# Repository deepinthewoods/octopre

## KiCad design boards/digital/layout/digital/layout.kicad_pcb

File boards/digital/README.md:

# digital

## Description

<!-- Brief description of this board -->

## Features

-

## Build Instructions

```bash
pcb build boards/digital
pcb layout boards/digital
```

## License

<!-- Add license information -->

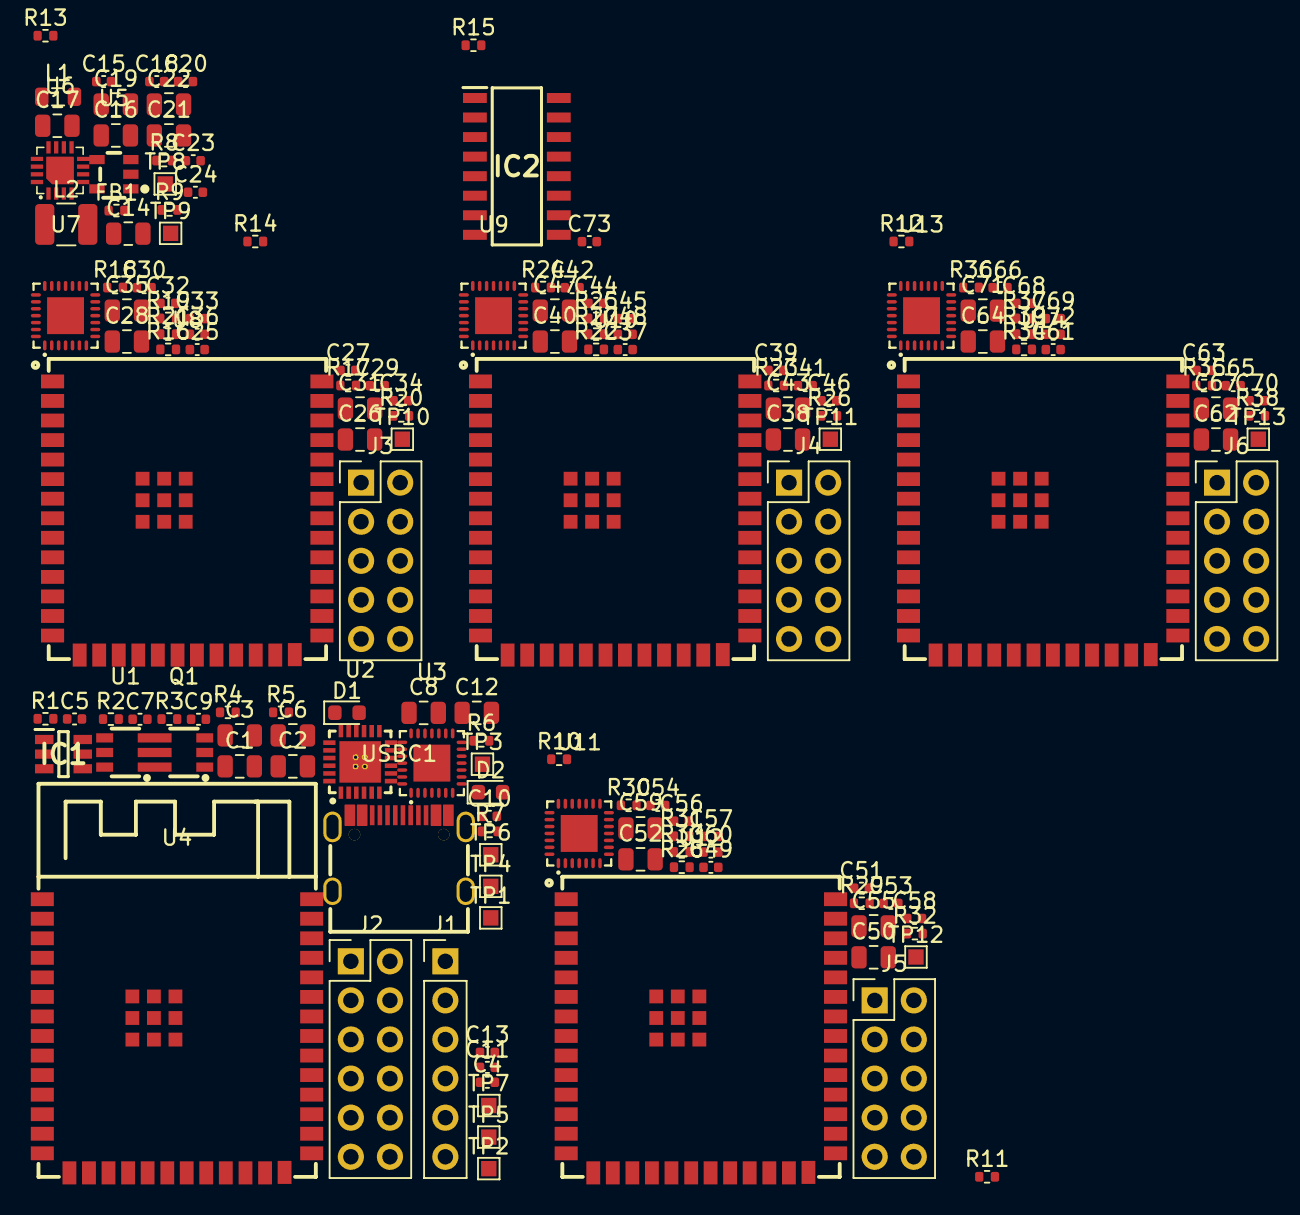
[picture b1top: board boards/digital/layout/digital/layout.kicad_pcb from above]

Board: 6 copper layers, 154 parts (0 on the bottom side), 144 nets, no tracks yet.

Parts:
C1, C2, C3, C6, C8, C12, C14, C16, C17, C19, C26, C28, C31, C35, C38, C40, C43, C47, C50, C52, C55, C59, C62, C64, C67, C71: GRM21BZ71E106KE15K; C_0805_2012Metric
C4, C5, C7, C9, C10, C11, C13, C15, C18, C20, C23, C25, C27, C29, C30, C32, C33, C34, C36, C37, C39, C41, C42, C44, C45, C46, C48, C49, C51, C53, C54, C56, C57, C58, C60, C61, C63, C65, C66, C68, C69, C70, C72, C73: GCM155R71H104KE02D; C_0402_1005Metric
C21, C22: GRM21BZ71A226ME15K; C_0805_2012Metric
C24: GRM1555CYA103GE01D; C_0402_1005Metric
D1, D2: LED GREEN; LED_0603_1608Metric
FB1: 600 100MHz; R_0402_1005Metric
IC1: USBLC6-2SC6
IC2: 74HC4052D
J1: 61300611121; PinHeader_1x06_P2.54mm_Vertical
J2: 2.54mm 6 x 2 THT Vertical Male; PinHeader_2x06_P2.54mm_Vertical
J3, J4, J5, J6: 61301021121; PinHeader_2x05_P2.54mm_Vertical
L1: 10uH; L_0805_2012Metric
L2: 2.2uH; L_1210_3225Metric
Q1: FS8205A
R1, R2: ERJ-2RKF5101X; R_0402_1005Metric
R3: ERJ-2RKF1202X; R_0402_1005Metric
R4: ERJ-2RKF1001X; R_0402_1005Metric
R5, R6, R16, R17, R22, R23, R28, R29, R34, R35: ERJ-2GE0R00X; R_0402_1005Metric
R7, R18, R19, R24, R25, R30, R31, R36, R37: ERJ-2RKF1002X; R_0402_1005Metric
R8: 64k; R_0402_1005Metric
R9: ERJ-2RKF2003X; R_0402_1005Metric
R10, R11, R12, R13, R14, R15, R20, R21, R26, R27, R32, R33, R38, R39: ERJ-2RKF33R0X; R_0402_1005Metric
TP1, TP2, TP3, TP4, TP5, TP6, TP7, TP8, TP9, TP10, TP11, TP12, TP13: ?; TestPoint_Pad_1.0x1.0mm
U1: HY2120-CB
U2: ?; SC8922QDLR
U3, U7, U9, U11, U13: ES8388
U4: ESP32-S3-WROOM-1-N16R8
U5: TPS7A2033PDBVR
U6: TPS62140RGTR
U8, U10, U12, U14: ESP32-S3-WROOM-1U-N16R8
USBC1: TYPE-C-31-M-12

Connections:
3V3_ANA: C16.1, FB1.1, L1.2, R5.1, R16.1, R22.1, R28.1, R34.1, TP8.1
3V3_DIG: C3.1, C4.1, C21.1, C22.1, C23.1, C31.1, C32.1, C43.1, C44.1, C55.1, C56.1, C67.1, C68.1, C73.1, D2.2, FB1.2, IC2.16, J1.6, L2.2, R4.1, R6.1, R7.1, R7.2, R9.1, R17.1, R18.1, R19.1, R23.1, R24.1, R25.1, R29.1, R30.1, R31.1, R35.1, R36.1, R37.1, TP9.1, U3.26, U4.2, U4.3, U4.27, U6.14, U7.26, U8.2, U9.26, U10.2, U11.26, U12.2, U13.26, U14.2
GND: C1.2, C2.2, C3.2, C4.2, C5.2, C6.2, C7.2, C8.2, C9.2, C10.2, C11.2, C12.2, C13.2, C14.2, C15.2, C16.2, C17.2, C18.2, C19.2, C20.2, C21.2, C22.2, C23.2, C24.2, C25.2, C26.2, C27.2, C28.2, C29.2, C30.2, C31.2, C32.2, C33.2, C34.2, C35.2, C36.2, C37.2, C38.2, C39.2, C40.2, C41.2, C42.2, C43.2, C44.2, C45.2, C46.2, C47.2, C48.2, C49.2, C50.2, C51.2, C52.2, C53.2, C54.2, C55.2, C56.2, C57.2, C58.2, C59.2, C60.2, C61.2, C62.2, C63.2, C64.2, C65.2, C66.2, C67.2, C68.2, C69.2, C70.2, C71.2, C72.2, C73.2, D1.1, D2.1, IC1.2, IC2.6, IC2.7, IC2.8, J1.5, J2.1, J2.2, J2.9, J2.10, J3.1, J3.2, J3.7, J3.8, J4.1, J4.2, J4.7, J4.8, J5.1, J5.2, J5.7, J5.8, J6.1, J6.2, J6.7, J6.8, Q1.1, R1.2, R2.2, R3.2, R8.2, U1.3, U1.6, U2.7, U2.10, U2.25, U3.4, U3.13, U3.18, U3.29, U4.1, U4.40, U4.41, U5.2, U6.6, U6.7, U6.8, U6.15, U6.16, U6.17, U7.4, U7.13, U7.18, U7.29, U8.1, U8.40, U8.41, U9.4, U9.13, U9.18, U9.29, U10.1, U10.40, U10.41, U11.4, U11.13, U11.18, U11.29, U12.1, U12.40, U12.41, U13.4, U13.13, U13.18, U13.29, U14.1, U14.40, U14.41, USBC1.1, USBC1.2, USBC1.3, USBC1.4, USBC1.A1B12, USBC1.B1A12
MASTER.BAT_PROT_POS: Q1.4, Q1.6, U1.1, U1.2
MASTER.BAT_RAW_POS: Q1.2, Q1.5, U1.4, U1.5
MASTER.CHG_SW: U2.1, U2.2, U2.23, U2.24
MASTER.JTAG_TCK: J1.3, U4.24
MASTER.JTAG_TDI: J1.1, U4.26
MASTER.JTAG_TDO: J1.2, U4.16
MASTER.JTAG_TMS: J1.4, U4.25
MASTER.M_ES_ADCVREF: C5.1, U3.19
MASTER.M_ES_AVDD: C6.1, C7.1, C10.1, C11.1, R5.2, U3.3, U3.16, U3.17
MASTER.M_ES_DVDD: C8.1, C9.1, R6.2, U3.2
MASTER.M_ES_VMID: C12.1, U3.20
MASTER.M_ES_VREF: C13.1, U3.10
MASTER.M_I2S_BCLK: U3.5, U4.5
MASTER.M_I2S_LRCLK: U3.7, U4.6
MASTER.M_I2S_MCLK: U3.1, U4.4
MASTER.M_I2S_SDIN: U3.6, U4.7
MASTER.M_I2S_SDOUT: U3.8, U4.12
MASTER.PG_CHG: D1.2, R4.2, U2.8
MASTER.USB_CC1: R1.1, USBC1.A5
MASTER.USB_CC2: R2.1, USBC1.B5
MASTER.USB_DN: IC1.3, IC1.4, TP4.1, U4.35, USBC1.A7, USBC1.B7
MASTER.USB_DP: IC1.1, IC1.6, TP5.1, U4.34, USBC1.A6, USBC1.B6
MASTER.USB_VBUS: C1.1, IC1.5, U2.4, USBC1.A4B9, USBC1.B4A9
MASTER.VSYS: TP7.1, U2.20, U2.21, U2.22
MCLK_S1: R10.2, U8.7
MCLK_S2: R11.2, U10.7
MCLK_S3: R12.2, U12.7
MCLK_S4: R13.2, U14.7
MCLK_SRC: R10.1, R11.1, R12.1, R13.1, TP3.1, U4.8
MUX_A: IC2.10, U4.11
MUX_B: IC2.9, U4.13
MUX_RX: IC2.3, U4.10
MUX_TX: IC2.13, U4.9
M_5V_ANA: C14.1, C15.1, J2.12, U5.1, U5.3
M_AIN_L: J2.3, U3.24
M_AIN_R: J2.4, U3.23
M_DAC_L: J2.5, U3.12
M_DAC_R: J2.6, U3.11
M_HP_L: J2.7, U3.15
M_HP_R: J2.8, U3.14
PWR.3V3_ANA_FILT: C17.1, C18.1, L1.1, U5.5
PWR.DIG_BUCK_FB: R8.1, R9.2, U6.5
PWR.DIG_BUCK_SS: C24.1, U6.9
PWR.DIG_BUCK_SW: L2.1, U6.1, U6.2, U6.3
S1_AIN_L: J3.3, U7.24
S1_AIN_R: J3.4, U7.23
S1_DAC_L: J3.5, U7.12
S1_DAC_R: J3.6, U7.11
S1_PWM_L: J3.9, R20.2
S1_PWM_R: J3.10, R21.2
S2_AIN_L: J4.3, U9.24
S2_AIN_R: J4.4, U9.23
S2_DAC_L: J4.5, U9.12
S2_DAC_R: J4.6, U9.11
S2_PWM_L: J4.9, R26.2
S2_PWM_R: J4.10, R27.2
S3_AIN_L: J5.3, U11.24
S3_AIN_R: J5.4, U11.23
S3_DAC_L: J5.5, U11.12
S3_DAC_R: J5.6, U11.11
S3_PWM_L: J5.9, R32.2
S3_PWM_R: J5.10, R33.2
S4_AIN_L: J6.3, U13.24
S4_AIN_R: J6.4, U13.23
S4_DAC_L: J6.5, U13.12
S4_DAC_R: J6.6, U13.11
S4_PWM_L: J6.9, R38.2
S4_PWM_R: J6.10, R39.2
SLAVE1.ES_ADCVREF: C25.1, U7.19
SLAVE1.ES_AVDD: C26.1, C27.1, C33.1, C34.1, R16.2, U7.3, U7.16, U7.17
SLAVE1.ES_DVDD: C28.1, C29.1, R17.2, U7.2
SLAVE1.ES_VMID: C35.1, U7.20
SLAVE1.ES_VREF: C36.1, U7.10
SLAVE1.I2S_BCLK: U7.5, U8.38
SLAVE1.I2S_LRCLK: U7.7, U8.34
SLAVE1.I2S_MCLK: TP10.1, U7.1, U8.39
SLAVE1.I2S_SDIN: U7.6, U8.35
SLAVE1.I2S_SDOUT: U7.8, U8.33
SLAVE1.PWM_L_INT: R20.1, U8.21
SLAVE1.PWM_R_INT: R21.1, U8.22
SLAVE1_EN: C30.1, R18.2, U4.30, U8.3
SLAVE1_GPIO0: R19.2, U4.14, U8.27
SLAVE1_RX: IC2.1, U8.37
SLAVE1_TX: IC2.12, U8.36
SLAVE2.ES_ADCVREF: C37.1, U9.19
SLAVE2.ES_AVDD: C38.1, C39.1, C45.1, C46.1, R22.2, U9.3, U9.16, U9.17
SLAVE2.ES_DVDD: C40.1, C41.1, R23.2, U9.2
SLAVE2.ES_VMID: C47.1, U9.20
SLAVE2.ES_VREF: C48.1, U9.10
SLAVE2.I2S_BCLK: U9.5, U10.38
SLAVE2.I2S_LRCLK: U9.7, U10.34
SLAVE2.I2S_MCLK: TP11.1, U9.1, U10.39
SLAVE2.I2S_SDIN: U9.6, U10.35
SLAVE2.I2S_SDOUT: U9.8, U10.33
SLAVE2.PWM_L_INT: R26.1, U10.21
SLAVE2.PWM_R_INT: R27.1, U10.22
SLAVE2_EN: C42.1, R24.2, U4.31, U10.3
SLAVE2_GPIO0: R25.2, U4.23, U10.27
SLAVE2_RX: IC2.5, U10.37
SLAVE2_TX: IC2.14, U10.36
SLAVE3.ES_ADCVREF: C49.1, U11.19
SLAVE3.ES_AVDD: C50.1, C51.1, C57.1, C58.1, R28.2, U11.3, U11.16, U11.17
SLAVE3.ES_DVDD: C52.1, C53.1, R29.2, U11.2
SLAVE3.ES_VMID: C59.1, U11.20
SLAVE3.ES_VREF: C60.1, U11.10
SLAVE3.I2S_BCLK: U11.5, U12.38
SLAVE3.I2S_LRCLK: U11.7, U12.34
SLAVE3.I2S_MCLK: TP12.1, U11.1, U12.39
SLAVE3.I2S_SDIN: U11.6, U12.35
SLAVE3.I2S_SDOUT: U11.8, U12.33
SLAVE3.PWM_L_INT: R32.1, U12.21
SLAVE3.PWM_R_INT: R33.1, U12.22
SLAVE3_EN: C54.1, R30.2, U4.32, U12.3
SLAVE3_GPIO0: R31.2, U4.28, U12.27
SLAVE3_RX: IC2.2, U12.37
SLAVE3_TX: IC2.15, U12.36
SLAVE4.ES_ADCVREF: C61.1, U13.19
SLAVE4.ES_AVDD: C62.1, C63.1, C69.1, C70.1, R34.2, U13.3, U13.16, U13.17
SLAVE4.ES_DVDD: C64.1, C65.1, R35.2, U13.2
SLAVE4.ES_VMID: C71.1, U13.20
SLAVE4.ES_VREF: C72.1, U13.10
SLAVE4.I2S_BCLK: U13.5, U14.38
SLAVE4.I2S_LRCLK: U13.7, U14.34
SLAVE4.I2S_MCLK: TP13.1, U13.1, U14.39
SLAVE4.I2S_SDIN: U13.6, U14.35
SLAVE4.I2S_SDOUT: U13.8, U14.33
SLAVE4.PWM_L_INT: R38.1, U14.21
SLAVE4.PWM_R_INT: R39.1, U14.22
SLAVE4_EN: C66.1, R36.2, U4.33, U14.3
SLAVE4_GPIO0: R37.2, U4.29, U14.27
SLAVE4_RX: IC2.4, U14.37
SLAVE4_TX: IC2.11, U14.36
TDM_BCLK: R14.2, U8.4, U10.4, U12.4, U14.4
TDM_BCLK_SRC: R14.1, TP1.1, U4.17
TDM_DATA_1: U4.19, U8.6
TDM_DATA_2: U4.20, U10.6
TDM_DATA_3: U4.21, U12.6
TDM_DATA_4: U4.22, U14.6
TDM_LRCLK: R15.2, U8.5, U10.5, U12.5, U14.5
TDM_LRCLK_SRC: R15.1, TP2.1, U4.18
VBAT: C2.1, C19.1, C20.1, J2.11, Q1.3, TP6.1, U2.16, U2.17, U2.18, U2.19, U6.10, U6.11, U6.12, U6.13

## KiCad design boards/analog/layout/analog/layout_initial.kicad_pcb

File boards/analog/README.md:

# analog

## Description

<!-- Brief description of this board -->

## Features

-

## Build Instructions

```bash
pcb build boards/analog
pcb layout boards/analog
```

## License

<!-- Add license information -->

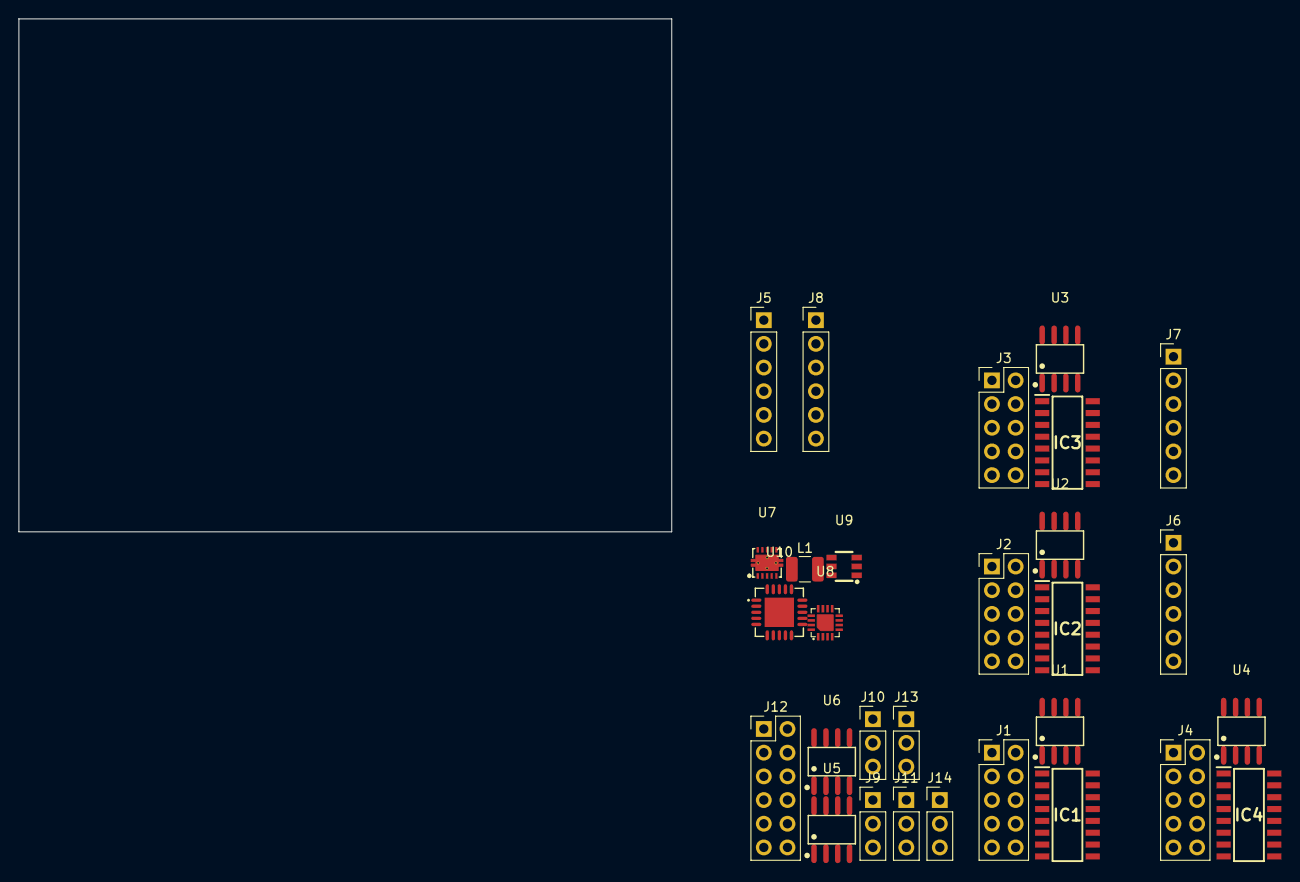
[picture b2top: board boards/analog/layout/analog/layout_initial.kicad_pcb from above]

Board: 6 copper layers, 70.0 x 55.0 mm, 29 parts (0 on the bottom side), 32 nets, no tracks yet.

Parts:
IC1, IC2, IC3, IC4: LM13700M
J1, J2, J3, J4: 61301021121; PinHeader_2x05_P2.54mm_Vertical
J5, J6, J7, J8: 61300611121; PinHeader_1x06_P2.54mm_Vertical
J9, J10, J11, J13, J14: 61300311121; PinHeader_1x03_P2.54mm_Vertical
J12: 2.54mm 6 x 2 THT Vertical Male; PinHeader_2x06_P2.54mm_Vertical
L1: 2.2uH; L_1210_3225Metric
U1, U2, U3, U4, U5, U6: OPA2134UA
U7: TPS7A3901DSCR
U8: TPS62140RGTR
U9: LM2776DBVR
U10: TPS7A4700RGWR

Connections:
5V_ANA: J12.12, U7.1, U7.2, U9.3, U9.4, U10.1, U10.20
AIN_1L: J5.1, J5.4, U1.3
AIN_2R: J5.2, J5.5, U1.5
AIN_3L: J6.1, J6.4, U2.3
AIN_4R: J6.2, J6.5, U2.5
AIN_5L: J7.1, J7.4, U3.3
AIN_6R: J7.2, J7.5, U3.5
AIN_7L: J8.1, J8.4, U4.3
AIN_8R: J8.2, J8.5, U4.5
CH12.PREAMP_OUT_L: J1.3, U1.1
CH12.PREAMP_OUT_R: J1.4, U1.7
CH34.PREAMP_OUT_L: J2.3, U2.1
CH34.PREAMP_OUT_R: J2.4, U2.7
CH56.PREAMP_OUT_L: J3.3, U3.1
CH56.PREAMP_OUT_R: J3.4, U3.7
CH78.PREAMP_OUT_L: J4.3, U4.1
CH78.PREAMP_OUT_R: J4.4, U4.7
GND: IC1.4, IC1.13, IC2.4, IC2.13, IC3.4, IC3.13, IC4.4, IC4.13, J1.1, J1.2, J1.7, J1.8, J2.1, J2.2, J2.7, J2.8, J3.1, J3.2, J3.7, J3.8, J4.1, J4.2, J4.7, J4.8, J5.3, J5.6, J6.3, J6.6, J7.3, J7.6, J8.3, J8.6, J9.3, J10.3, J11.3, J12.1, J12.2, J12.9, J12.10, U6.3, U6.5, U7.4, U7.11, U8.6, U8.8, U8.15, U8.16, U8.17, U9.2, U10.6, U10.7, U10.10, U10.21
MSTR.EXT_IN_L: J10.1, J13.3
MSTR.EXT_IN_R: J10.2, J14.3
MSTR.HDR_AIN_L: J12.3, J13.1
MSTR.HDR_AIN_R: J12.4, J14.1
MSTR.HDR_DAC_L: J12.5, U5.3
MSTR.HDR_DAC_R: J12.6, U5.5
MSTR.SUM_OUT_L: J13.2, U6.1
MSTR.SUM_OUT_R: J14.2, U6.7
PSU.6V_PRE: L1.2, U8.14, U10.13, U10.15, U10.16
PSU.BUCK_SW: L1.1, U8.1, U8.2, U8.3
PSU.NEG5V_RAW: U7.5, U9.1
VBAT: J12.11, U8.7, U8.10, U8.11, U8.12, U8.13
VN3: IC1.6, IC2.6, IC3.6, IC4.6, U1.4, U2.4, U3.4, U4.4, U5.4, U6.4, U7.6
VP3: IC1.2, IC1.11, IC1.15, IC2.2, IC2.11, IC2.15, IC3.2, IC3.11, IC3.15, IC4.2, IC4.11, IC4.15, U1.8, U2.8, U3.8, U4.8, U5.8, U6.8, U7.10

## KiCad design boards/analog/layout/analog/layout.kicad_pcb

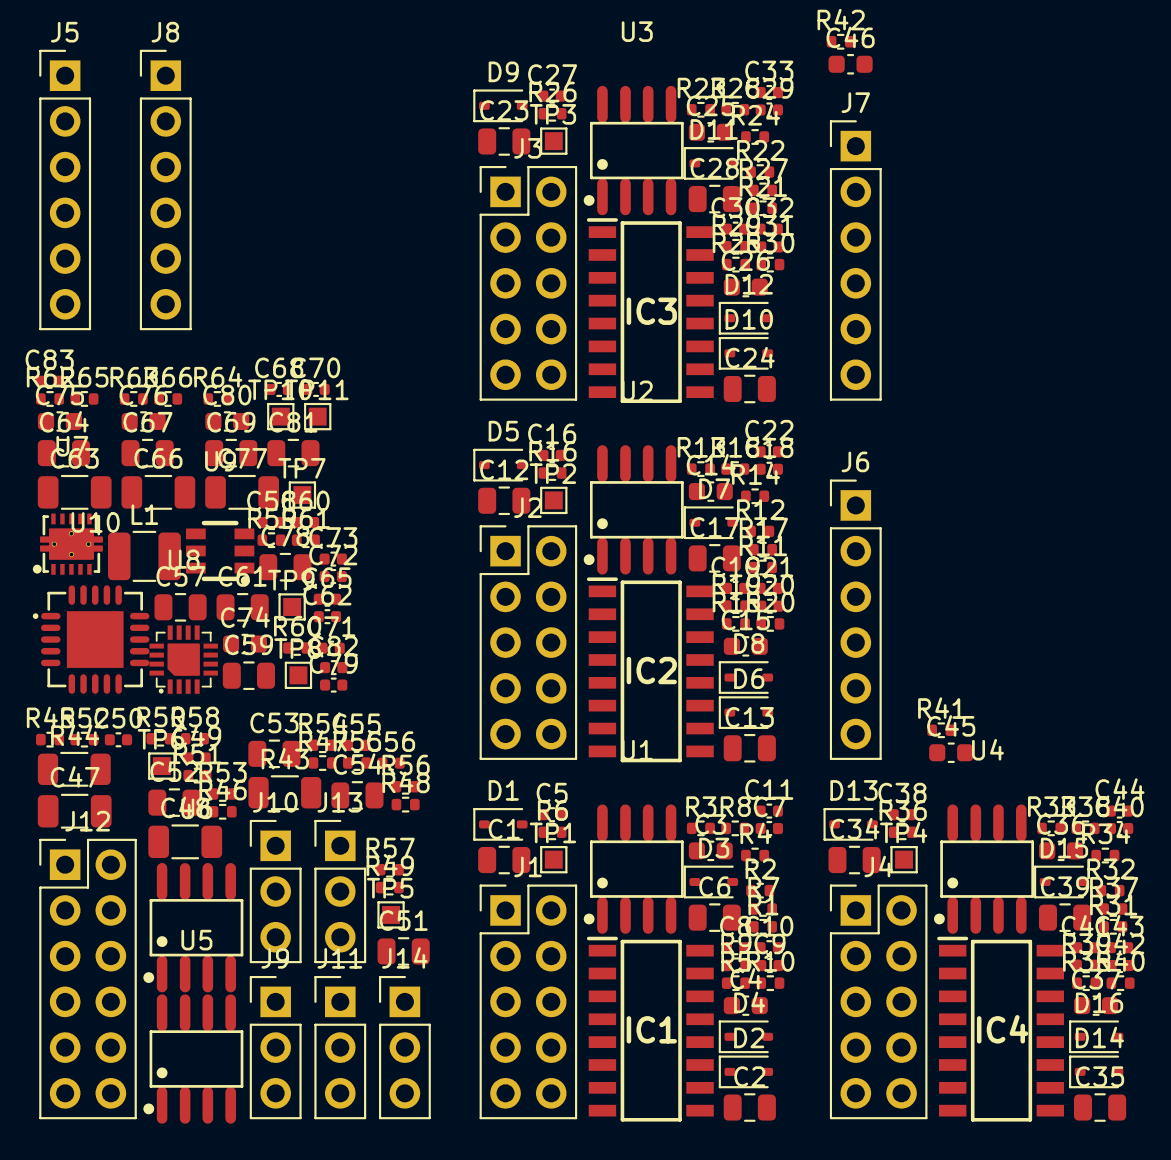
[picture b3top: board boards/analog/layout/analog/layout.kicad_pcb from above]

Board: 6 copper layers, 205 parts (0 on the bottom side), 128 nets, no tracks yet.

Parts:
C1, C2, C6, C12, C13, C17, C23, C24, C28, C34, C35, C39, C51, C52, C53, C54, C57, C59, C61, C64, C67, C78, C81: GRM21BZ71E106KE15K; C_0805_2012Metric
C3, C4, C14, C15, C25, C26, C36, C37, C45, C46, C74, C75, C76, C80: GCM188R71E105KA64D; C_0603_1608Metric
C5, C7, C8, C9, C10, C11, C16, C18, C19, C20, C21, C22, C27, C29, C30, C31, C32, C33, C38, C40, C41, C42, C43, C44, C49, C50, C55, C56, C58, C60, C62, C65, C68, C70, C79, C82: GCM155R71H104KE02D; C_0402_1005Metric
C47, C48: 220uF; C_1206_3216Metric
C63, C66: 100uF 4.5V; C_1206_3216Metric
C69: GRM21BZ71A226ME15K; C_0805_2012Metric
C71, C72, C73, C83: GRM1555CYA103GE01D; C_0402_1005Metric
C77: 47uF 7.5V X5R; C_1206_3216Metric
D1, D2, D3, D4, D5, D6, D7, D8, D9, D10, D11, D12, D13, D14, D15, D16: Standard; D_SOD-323
IC1, IC2, IC3, IC4: LM13700M
J1, J2, J3, J4: 61301021121; PinHeader_2x05_P2.54mm_Vertical
J5, J6, J7, J8: 61300611121; PinHeader_1x06_P2.54mm_Vertical
J9, J10, J11, J13, J14: 61300311121; PinHeader_1x03_P2.54mm_Vertical
J12: 2.54mm 6 x 2 THT Vertical Male; PinHeader_2x06_P2.54mm_Vertical
L1: 2.2uH; L_1210_3225Metric
R1, R2, R5, R6, R11, R12, R15, R16, R21, R22, R25, R26, R31, R32, R35, R36, R49, R50, R51, R52, R53, R54, R55, R56, R57, R58: ERJ-2RKF1002X; R_0402_1005Metric
R3, R4, R13, R14, R23, R24, R33, R34: ERJ-2RKF3300X; R_0402_1005Metric
R7, R8, R17, R18, R27, R28, R37, R38, R45, R46, R61, R66: ERJ-2GE0R00X; R_0402_1005Metric
R9, R10, R19, R20, R29, R30, R39, R40: ERJ-2RKF1001X; R_0402_1005Metric
R41, R42: ERJ-2RKF2201X; R_0402_1005Metric
R43, R44: 0; R_1206_3216Metric
R47, R48: ERJ-2RKF1000X; R_0402_1005Metric
R59: 60k; R_0402_1005Metric
R60: ERJ-2RKF3903X; R_0402_1005Metric
R62, R64: ERJ-2RKF1203X; R_0402_1005Metric
R63, R65: ERJ-2RKF1803X; R_0402_1005Metric
TP1, TP2, TP3, TP4, TP5, TP6, TP7, TP8, TP9, TP10, TP11: ?; TestPoint_Pad_1.0x1.0mm
U1, U2, U3, U4, U5, U6: OPA2134UA
U7: TPS7A3901DSCR
U8: TPS62140RGTR
U9: LM2776DBVR
U10: TPS7A4700RGWR

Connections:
5V_ANA: C59.1, C60.1, C74.1, C77.1, C81.1, C82.1, J12.12, R66.1, TP7.1, U7.1, U7.2, U9.3, U9.4, U10.1, U10.20
AIN_1L: C1.1, C45.2, D1.1, D2.2, J5.1, J5.4, U1.3
AIN_2R: C2.1, C46.2, D3.1, D4.2, J5.2, J5.5, U1.5
AIN_3L: C12.1, D5.1, D6.2, J6.1, J6.4, U2.3
AIN_4R: C13.1, D7.1, D8.2, J6.2, J6.5, U2.5
AIN_5L: C23.1, D9.1, D10.2, J7.1, J7.4, U3.3
AIN_6R: C24.1, D11.1, D12.2, J7.2, J7.5, U3.5
AIN_7L: C34.1, D13.1, D14.2, J8.1, J8.4, U4.3
AIN_8R: C35.1, D15.1, D16.2, J8.2, J8.5, U4.5
CH12.BUF_IN_L: IC1.7, R7.2
CH12.BUF_IN_R: IC1.10, R8.2
CH12.OD_BIAS_L: IC1.1, R1.2
CH12.OD_BIAS_R: IC1.16, R2.2
CH12.OD_CTRL_L: C10.1, R1.1, R9.2
CH12.OD_CTRL_R: C11.1, R2.1, R10.2
CH12.OD_IN_L: C3.2, IC1.3
CH12.OD_IN_R: C4.2, IC1.14
CH12.OD_OUT_L: IC1.5, R7.1
CH12.OD_OUT_R: IC1.12, R8.1
CH12.PREAMP_FB_L: R3.1, R5.2, U1.2
CH12.PREAMP_FB_R: R4.1, R6.2, U1.6
CH12.PREAMP_OUT_L: J1.3, R5.1, U1.1
CH12.PREAMP_OUT_R: J1.4, R6.1, U1.7
CH34.BUF_IN_L: IC2.7, R17.2
CH34.BUF_IN_R: IC2.10, R18.2
CH34.OD_BIAS_L: IC2.1, R11.2
CH34.OD_BIAS_R: IC2.16, R12.2
CH34.OD_CTRL_L: C21.1, R11.1, R19.2
CH34.OD_CTRL_R: C22.1, R12.1, R20.2
CH34.OD_IN_L: C14.2, IC2.3
CH34.OD_IN_R: C15.2, IC2.14
CH34.OD_OUT_L: IC2.5, R17.1
CH34.OD_OUT_R: IC2.12, R18.1
CH34.PREAMP_FB_L: R13.1, R15.2, U2.2
CH34.PREAMP_FB_R: R14.1, R16.2, U2.6
CH34.PREAMP_OUT_L: J2.3, R15.1, U2.1
CH34.PREAMP_OUT_R: J2.4, R16.1, U2.7
CH56.BUF_IN_L: IC3.7, R27.2
CH56.BUF_IN_R: IC3.10, R28.2
CH56.OD_BIAS_L: IC3.1, R21.2
CH56.OD_BIAS_R: IC3.16, R22.2
CH56.OD_CTRL_L: C32.1, R21.1, R29.2
CH56.OD_CTRL_R: C33.1, R22.1, R30.2
CH56.OD_IN_L: C25.2, IC3.3
CH56.OD_IN_R: C26.2, IC3.14
CH56.OD_OUT_L: IC3.5, R27.1
CH56.OD_OUT_R: IC3.12, R28.1
CH56.PREAMP_FB_L: R23.1, R25.2, U3.2
CH56.PREAMP_FB_R: R24.1, R26.2, U3.6
CH56.PREAMP_OUT_L: J3.3, R25.1, U3.1
CH56.PREAMP_OUT_R: J3.4, R26.1, U3.7
CH78.BUF_IN_L: IC4.7, R37.2
CH78.BUF_IN_R: IC4.10, R38.2
CH78.OD_BIAS_L: IC4.1, R31.2
CH78.OD_BIAS_R: IC4.16, R32.2
CH78.OD_CTRL_L: C43.1, R31.1, R39.2
CH78.OD_CTRL_R: C44.1, R32.1, R40.2
CH78.OD_IN_L: C36.2, IC4.3
CH78.OD_IN_R: C37.2, IC4.14
CH78.OD_OUT_L: IC4.5, R37.1
CH78.OD_OUT_R: IC4.12, R38.1
CH78.PREAMP_FB_L: R33.1, R35.2, U4.2
CH78.PREAMP_FB_R: R34.1, R36.2, U4.6
CH78.PREAMP_OUT_L: J4.3, R35.1, U4.1
CH78.PREAMP_OUT_R: J4.4, R36.1, U4.7
GND: C1.2, C2.2, C5.2, C6.2, C7.2, C8.2, C9.2, C10.2, C11.2, C12.2, C13.2, C16.2, C17.2, C18.2, C19.2, C20.2, C21.2, C22.2, C23.2, C24.2, C27.2, C28.2, C29.2, C30.2, C31.2, C32.2, C33.2, C34.2, C35.2, C38.2, C39.2, C40.2, C41.2, C42.2, C43.2, C44.2, C49.2, C50.2, C51.2, C52.2, C55.2, C56.2, C57.2, C58.2, C59.2, C60.2, C61.2, C62.2, C63.2, C64.2, C65.2, C66.2, C67.2, C68.2, C69.2, C70.2, C71.2, C74.2, C75.2, C77.2, C78.2, C79.2, C80.2, C81.2, C82.2, C83.2, IC1.4, IC1.13, IC2.4, IC2.13, IC3.4, IC3.13, IC4.4, IC4.13, J1.1, J1.2, J1.7, J1.8, J2.1, J2.2, J2.7, J2.8, J3.1, J3.2, J3.7, J3.8, J4.1, J4.2, J4.7, J4.8, J5.3, J5.6, J6.3, J6.6, J7.3, J7.6, J8.3, J8.6, J9.3, J10.3, J11.3, J12.1, J12.2, J12.9, J12.10, R3.2, R4.2, R13.2, R14.2, R23.2, R24.2, R33.2, R34.2, R43.2, R44.2, R59.2, R61.2, R62.2, R64.2, U6.3, U6.5, U7.4, U7.11, U8.6, U8.8, U8.15, U8.16, U8.17, U9.2, U10.6, U10.7, U10.10, U10.21
MIC1.MIC_BIAS: C45.1, R41.2
MIC2.MIC_BIAS: C46.1, R42.2
MSTR.EXT_IN_L: J10.1, J13.3
MSTR.EXT_IN_R: J10.2, J14.3
MSTR.HDR_AIN_L: C53.2, J12.3, J13.1
MSTR.HDR_AIN_R: C54.2, J12.4, J14.1
MSTR.HDR_DAC_L: J12.5, U5.3
MSTR.HDR_DAC_R: J12.6, U5.5
MSTR.HDR_HP_L: C47.1, J12.7
MSTR.HDR_HP_R: C48.1, J12.8
MSTR.HP_OUT_L: C47.2, J9.1, R43.1
MSTR.HP_OUT_R: C48.2, J9.2, R44.1
MSTR.LINE_BUF_L: R45.1, R47.1, U5.1
MSTR.LINE_BUF_R: R46.1, R48.1, U5.7
MSTR.LINE_FB_L: R45.2, U5.2
MSTR.LINE_FB_R: R46.2, U5.6
MSTR.LINE_OUT_L: C51.1, J11.1, R47.2, TP5.1
MSTR.LINE_OUT_R: C52.1, J11.2, R48.2
MSTR.SUM_FB_L: R49.2, R51.2, R52.2, R53.2, R54.2, U6.2
MSTR.SUM_FB_R: R50.2, R55.2, R56.2, R57.2, R58.2, U6.6
MSTR.SUM_OUT_L: C53.1, J13.2, R49.1, TP6.1, U6.1
MSTR.SUM_OUT_R: C54.1, J14.2, R50.1, U6.7
PSU.6V_PRE: C69.1, C70.1, C78.1, C79.1, L1.2, R60.1, TP8.1, U8.14, U10.13, U10.15, U10.16
PSU.BUCK_FB: R59.1, R60.2, U8.5
PSU.BUCK_SS: C71.1, U8.9
PSU.BUCK_SW: L1.1, U8.1, U8.2, U8.3
PSU.CP_FLY_N: C76.2, U9.6
PSU.CP_FLY_P: C76.1, U9.5
PSU.LDO_NR: C80.1, U10.14
PSU.LDO_SENSE: R66.2, U10.3
PSU.NEG5V_RAW: C57.1, C58.1, C75.1, TP9.1, U7.5, U9.1
PSU.TPS39_BUF: R61.1, U7.8
PSU.TPS39_FBN: C72.1, R62.1, R63.2, U7.7
PSU.TPS39_FBP: C73.1, R64.1, R65.2, U7.9
PSU.TPS39_NRSS: C83.1, U7.3
S1_DAC_L: C3.1, J1.5
S1_DAC_R: C4.1, J1.6
S1_PWM_L: J1.9, R9.1
S1_PWM_R: J1.10, R10.1
S2_DAC_L: C14.1, J2.5
S2_DAC_R: C15.1, J2.6
S2_PWM_L: J2.9, R19.1
S2_PWM_R: J2.10, R20.1
S3_DAC_L: C25.1, J3.5
S3_DAC_R: C26.1, J3.6
S3_PWM_L: J3.9, R29.1
S3_PWM_R: J3.10, R30.1
S4_DAC_L: C36.1, J4.5
S4_DAC_R: C37.1, J4.6
S4_PWM_L: J4.9, R39.1
S4_PWM_R: J4.10, R40.1
SUM_L_1: IC1.8, R51.1, TP1.1
SUM_L_2: IC2.8, R52.1, TP2.1
SUM_L_3: IC3.8, R53.1, TP3.1
SUM_L_4: IC4.8, R54.1, TP4.1
SUM_R_1: IC1.9, R55.1
SUM_R_2: IC2.9, R56.1
SUM_R_3: IC3.9, R57.1
SUM_R_4: IC4.9, R58.1
VBAT: C67.1, C68.1, J12.11, U8.7, U8.10, U8.11, U8.12, U8.13
VN3: C5.1, C6.1, C8.1, C16.1, C17.1, C19.1, C27.1, C28.1, C30.1, C38.1, C39.1, C41.1, C49.1, C55.1, C61.1, C62.1, C63.1, C72.2, D1.2, D3.2, D5.2, D7.2, D9.2, D11.2, D13.2, D15.2, IC1.6, IC2.6, IC3.6, IC4.6, R63.1, TP10.1, U1.4, U2.4, U3.4, U4.4, U5.4, U6.4, U7.6
VP3: C7.1, C9.1, C18.1, C20.1, C29.1, C31.1, C40.1, C42.1, C50.1, C56.1, C64.1, C65.1, C66.1, C73.2, D2.1, D4.1, D6.1, D8.1, D10.1, D12.1, D14.1, D16.1, IC1.2, IC1.11, IC1.15, IC2.2, IC2.11, IC2.15, IC3.2, IC3.11, IC3.15, IC4.2, IC4.11, IC4.15, R41.1, R42.1, R65.1, TP11.1, U1.8, U2.8, U3.8, U4.8, U5.8, U6.8, U7.10

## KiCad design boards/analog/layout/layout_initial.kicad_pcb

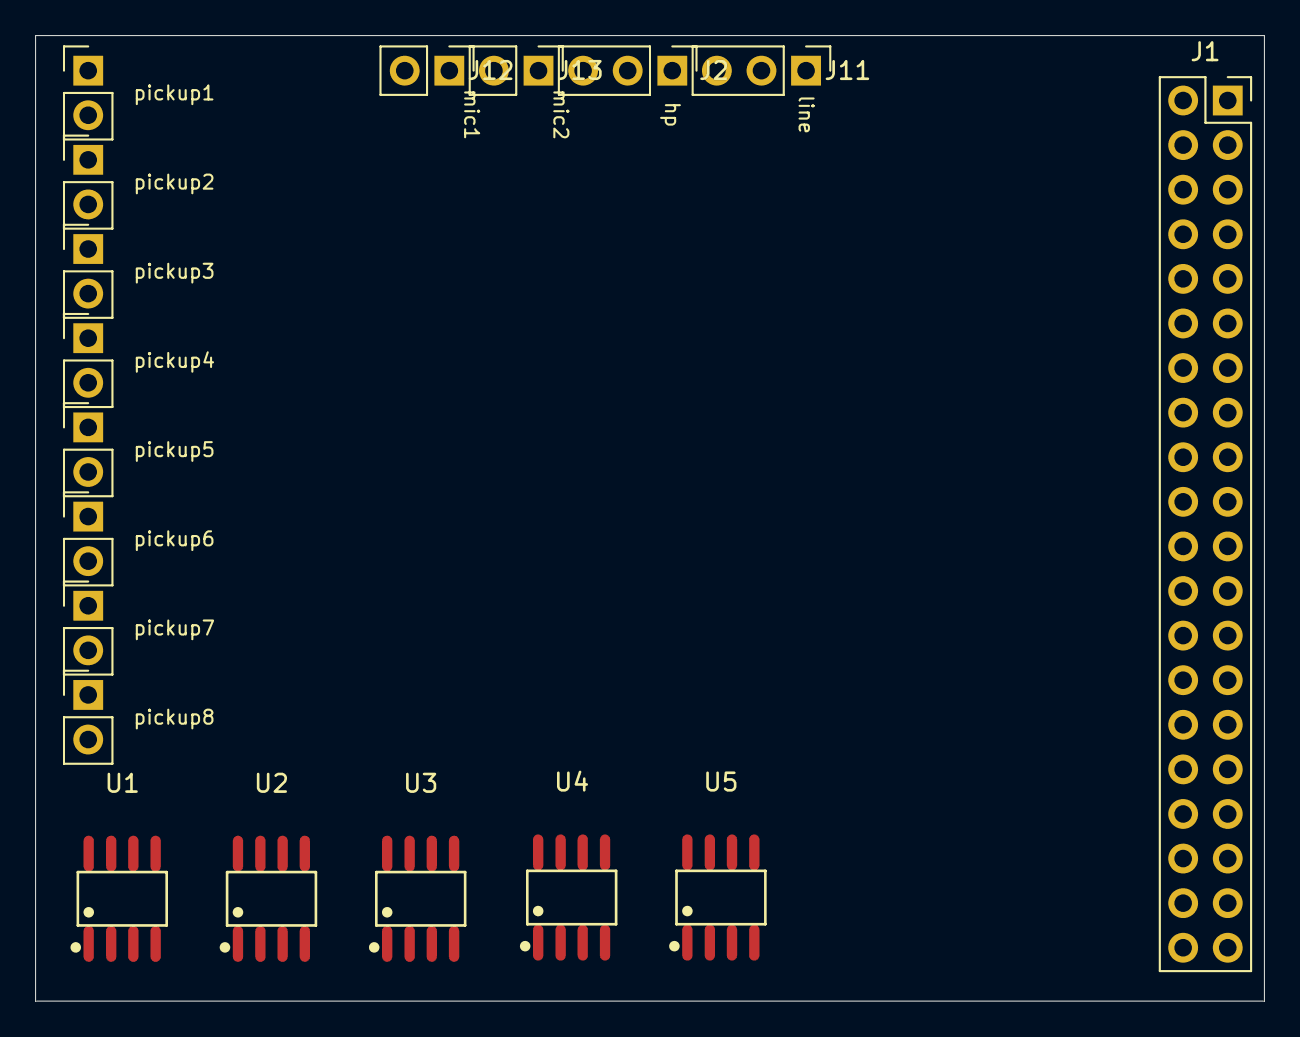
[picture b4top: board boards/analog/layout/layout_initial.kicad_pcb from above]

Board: 6 copper layers, 70.0 x 55.0 mm, 18 parts (0 on the bottom side), 8 nets, no tracks yet.

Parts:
J1: 2.54mm 20 x 2 THT Vertical Female; PinSocket_2x20_P2.54mm_Vertical
J2, J11: 61300311121; PinHeader_1x03_P2.54mm_Vertical
J3, J4, J5, J6, J7, J8, J9, J10, J12, J13: 61300211121; PinHeader_1x02_P2.54mm_Vertical
U1, U2, U3, U4, U5: OPA2134UA

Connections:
3V3_ANA: J1.4, J1.5, U1.8, U2.8, U3.8, U4.8, U5.8
3V3_DIG: J1.25, J1.26
GND: J1.1, J1.2, J1.3, J1.6, J1.23, J1.24, J2.3, J3.2, J4.2, J5.2, J6.2, J7.2, J8.2, J9.2, J10.2, J11.3, J12.2, J13.2, U1.4, U2.4, U3.4, U4.4, U5.4
J_CONN.NC_PH_Pin_40: J1.21, J1.22, J1.27, J1.28, J1.29, J1.30, J1.31, J1.32, J1.33, J1.34, J1.35, J1.36, J1.37, J1.38, J1.39, J1.40
LINE_BUF_L: U1.1, U1.2
LINE_BUF_R: U1.6, U1.7
LINE_L: J1.9, U1.3
LINE_R: J1.10, U1.5

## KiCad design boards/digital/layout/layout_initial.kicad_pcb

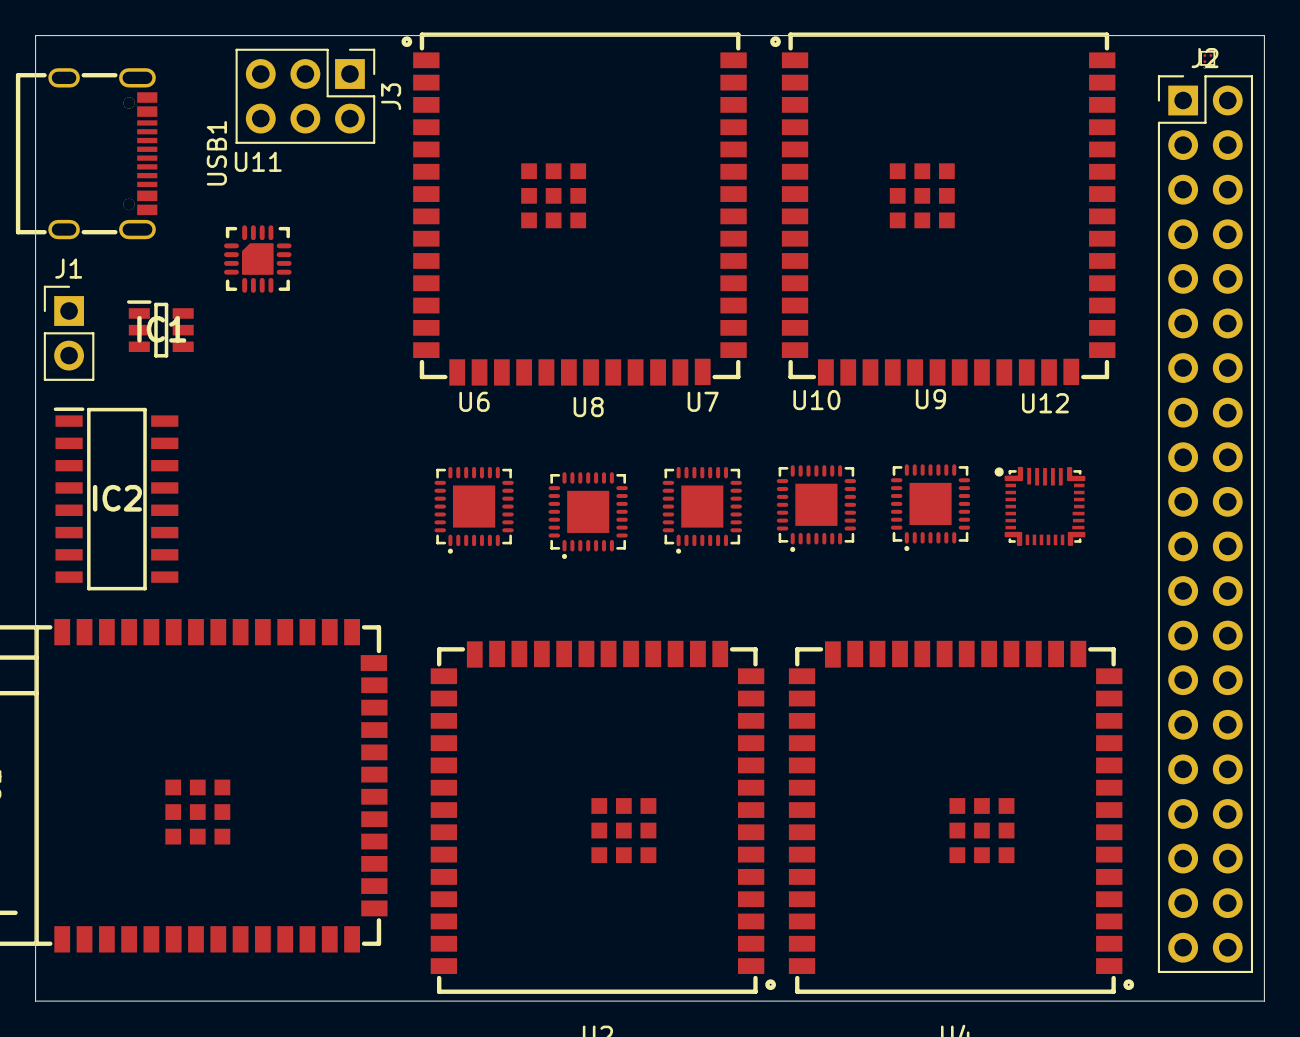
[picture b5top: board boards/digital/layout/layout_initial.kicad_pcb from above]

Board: 6 copper layers, 70.0 x 55.0 mm, 19 parts (0 on the bottom side), 65 nets, no tracks yet.

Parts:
IC1: USBLC6-2SC6
IC2: 74HC4052D
J1: 61300211121; PinHeader_1x02_P2.54mm_Vertical
J2: 61304021121; PinHeader_2x20_P2.54mm_Vertical
J3: 61300621121; PinHeader_2x03_P2.54mm_Vertical
U1: ESP32-S3-WROOM-1-N16R8
U2, U3, U4, U5: ESP32-S3-WROOM-1U-N16R8
U6, U7, U8, U9, U10: ES8388
U11: TPS62130RGTR
U12: BQ25798RQMR
U13: LP5907A33YKMR
USB1: USB4105-GF-A

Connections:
3V3_ANA: J2.4, J2.5, U6.3, U6.16, U6.17, U7.3, U7.17, U8.3, U8.17, U9.3, U9.17, U10.3, U10.17
3V3_DIG: IC2.16, J2.25, J2.26, J3.1, U1.2, U2.2, U3.2, U4.2, U5.2, U6.2, U7.2, U7.26, U8.2, U9.2, U9.26, U10.2, U11.14, U12.12, U12.13
5V_USB: IC1.5, U12.2, U12.3, U12.9, USB1.A4, USB1.A9, USB1.B4, USB1.B9
BQ_INT: U1.24, U12.21
BQ_PMID: U12.26, U12.28, U12.29
BQ_STAT: U1.16, U12.1
BUCK_SW: U11.1, U11.2, U11.3
ES_LIN1_1: J2.11, U6.24
ES_LIN1_2: J2.13, U7.24
ES_LIN1_3: J2.15, U8.24
ES_LIN1_4: J2.17, U9.24
ES_LIN1_5: J2.19, U10.24
ES_RIN1_1: J2.12, U6.23
ES_RIN1_2: J2.14, U7.23
ES_RIN1_3: J2.16, U8.23
ES_RIN1_4: J2.18, U9.23
ES_RIN1_5: J2.20, U10.23
ES_SDIN_1: U1.12, U6.6
ES_SDIN_2: U2.12, U7.6
ES_SDIN_3: U3.12, U8.6
ES_SDIN_4: U4.12, U9.6
ES_SDIN_5: U5.12, U10.6
ES_SDOUT_1: U1.17, U6.8
ES_SDOUT_2: U2.17, U7.8
ES_SDOUT_3: U3.17, U8.8
ES_SDOUT_4: U4.17, U9.8
ES_SDOUT_5: U5.17, U10.8
GND: IC1.2, IC2.6, IC2.7, IC2.8, J1.2, J2.1, J2.2, J2.3, J2.6, J2.23, J2.24, J3.2, U1.1, U1.40, U1.41, U2.1, U2.40, U2.41, U3.1, U3.40, U3.41, U4.1, U4.40, U4.41, U5.1, U5.40, U5.41, U6.4, U6.13, U6.18, U6.26, U6.29, U7.4, U7.18, U7.29, U8.4, U8.18, U8.26, U8.29, U9.4, U9.18, U9.29, U10.4, U10.18, U10.26, U10.29, U11.6, U11.7, U11.8, U11.15, U11.16, U11.17, U12.27, U13.B2, USB1.1, USB1.A1, USB1.A12, USB1.B1, USB1.B12
HP_L: J2.7, U6.12
HP_R: J2.8, U6.11
I2C_SCL: J2.22, U1.38, U2.38, U3.38, U4.38, U5.38, U6.28, U7.28, U8.28, U9.28, U10.28, U12.14
I2C_SDA: J2.21, U1.39, U2.39, U3.39, U4.39, U5.39, U6.27, U7.27, U8.27, U9.27, U10.27, U12.15
J_CONN.NC_PH_Pin_34: J2.27, J2.28, J2.29, J2.30, J2.31, J2.32, J2.33, J2.34, J2.35, J2.36, J2.37, J2.38, J2.39, J2.40, J3.3, J3.4, J3.5, J3.6, U1.4, U1.15, U1.22, U1.23, U1.27, U1.36, U1.37, U2.4, U2.9, U2.10, U2.11, U2.13, U2.14, U2.15, U2.16, U2.18, U2.19, U2.20, U2.21, U2.22, U2.23, U2.24, U2.25, U2.26, U2.28, U2.29, U2.30, U2.31, U2.32, U2.33, U2.34, U2.35, U3.4, U3.9, U3.10, U3.11, U3.13, U3.14, U3.15, U3.16, U3.18, U3.19, U3.20, U3.21, U3.22, U3.23, U3.24, U3.25, U3.26, U3.28, U3.29, U3.30, U3.31, U3.32, U3.33, U3.34, U3.35, U4.4, U4.9, U4.10, U4.11, U4.13, U4.14, U4.15, U4.16, U4.18, U4.19, U4.20, U4.21, U4.22, U4.23, U4.24, U4.25, U4.26, U4.28, U4.29, U4.30, U4.31, U4.32, U4.33, U4.34, U4.35, U5.4, U5.9, U5.10, U5.11, U5.13, U5.14, U5.15, U5.16, U5.18, U5.19, U5.20, U5.21, U5.22, U5.23, U5.24, U5.25, U5.26, U5.28, U5.29, U5.30, U5.31, U5.32, U5.33, U5.34, U5.35, U6.9, U6.21, U6.22, U6.25, U7.9, U7.11, U7.12, U7.13, U7.14, U7.15, U7.16, U7.21, U7.22, U7.25, U8.9, U8.11, U8.12, U8.13, U8.14, U8.15, U8.16, U8.21, U8.22, U8.25, U9.9, U9.11, U9.12, U9.13, U9.14, U9.15, U9.16, U9.21, U9.22, U9.25, U10.9, U10.11, U10.12, U10.13, U10.14, U10.15, U10.16, U10.21, U10.22, U10.25, U12.8, U12.10, USB1.A8, USB1.B8
LINE_L: J2.9, U6.15
LINE_R: J2.10, U6.14
MUX_A: IC2.10, U1.20
MUX_B: IC2.9, U1.21
SLAVE_EN_1: U1.32, U2.3
SLAVE_EN_2: U1.33, U3.3
SLAVE_EN_3: U1.34, U4.3
SLAVE_EN_4: U1.35, U5.3
SLAVE_GPIO0_1: U1.28, U2.27
SLAVE_GPIO0_2: U1.29, U3.27
SLAVE_GPIO0_3: U1.30, U4.27
SLAVE_GPIO0_4: U1.31, U5.27
SLAVE_RX_1: IC2.1, U2.36
SLAVE_RX_2: IC2.5, U3.36
SLAVE_RX_3: IC2.2, U4.36
SLAVE_RX_4: IC2.4, U5.36
SLAVE_TX_1: IC2.12, U2.37
SLAVE_TX_2: IC2.14, U3.37
SLAVE_TX_3: IC2.15, U4.37
SLAVE_TX_4: IC2.11, U5.37
TDM_BCLK: U2.5, U3.5, U4.5, U5.5, U6.5, U7.5, U8.5, U9.5, U10.5
TDM_DATA_1: U1.8, U2.8
TDM_DATA_2: U1.9, U3.8
TDM_DATA_3: U1.10, U4.8
TDM_DATA_4: U1.11, U5.8
TDM_LRCLK: U2.6, U3.6, U4.6, U5.6, U6.7, U7.7, U8.7, U9.7, U10.7
TDM_MCLK: U1.7, U2.7, U3.7, U4.7, U5.7, U6.1, U7.1, U8.1, U9.1, U10.1
UART_MUX_RX: IC2.3, U1.19
UART_MUX_TX: IC2.13, U1.18
USB_DM: IC1.3, IC1.4, U1.13, U12.7, USB1.A7, USB1.B7
USB_DP: IC1.1, IC1.6, U1.14, U12.6, USB1.A6, USB1.B6
VBAT: J1.1, U11.10, U11.11, U11.12, U11.13, U12.18, U12.22, U12.23, U13.A1, U13.B1
